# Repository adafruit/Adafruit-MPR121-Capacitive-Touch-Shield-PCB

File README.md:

## Adafruit MPR121 Capacitive Touch Shield PCB
<a href="http://www.adafruit.com/products/2024"><br/>
Click here to purchase one from the Adafruit shop</a>

This touch-able add on shield for Arduinos will inspire your next interactive project with 12 capacitive touch sensors. Capacitive touch sensing works by detecting when a person (or animal) has touched one of the sensor electrodes. Capacitive touch sensing used for stuff like touch-reactive tablets and phones, as well as control panels for appliances, which is where you may have used it before. This shield allows you to create electronics that can react to human touch, with up to 12 individual sensors.

The shield has 12 'figure 8' holes in it that can be gripped onto with alligator clip cables. Attach one side of the clip to the shield and the other side to something electrically conductive (like metal) or full of water (like vegetables or fruit!) Then start up our handy Arduino library to detect when the object is touched. That's pretty much it, very easy! For advanced users, you can also solder to a pad to make a slimmer & more permanent connection. Works great with any Arduino as it only uses the I2C pins (SCL & SDA).

It uses the same chip as our MPR121 12-Key Capacitive Touch Sensor Breakout so you can duplicate the library and code! We have examples for reading touches. Using an Arduino Leonardo and a little bit of creativity you can use it to turn touches into keyboard KeyUp/KeyDown presses (so you can make a veggie-keyboard) or pair it with our Music Maker shield to create an audio player that will play a sound per sensor (fruit drums!)

PCB files for the Adafruit MPR121 Capacitive Touch Shield. The format is EagleCAD schematic and board layout
- https://www.adafruit.com/product/2024

### License

Adafruit invests time and resources providing this open source design, please support Adafruit and open-source hardware by purchasing products from [Adafruit](https://www.adafruit.com)!

All text above must be included in any redistribution

Designed by Limor Fried/Ladyada for Adafruit Industries.
Creative Commons Attribution/Share-Alike, all text above must be included in any redistribution.
See license.txt for additional information.

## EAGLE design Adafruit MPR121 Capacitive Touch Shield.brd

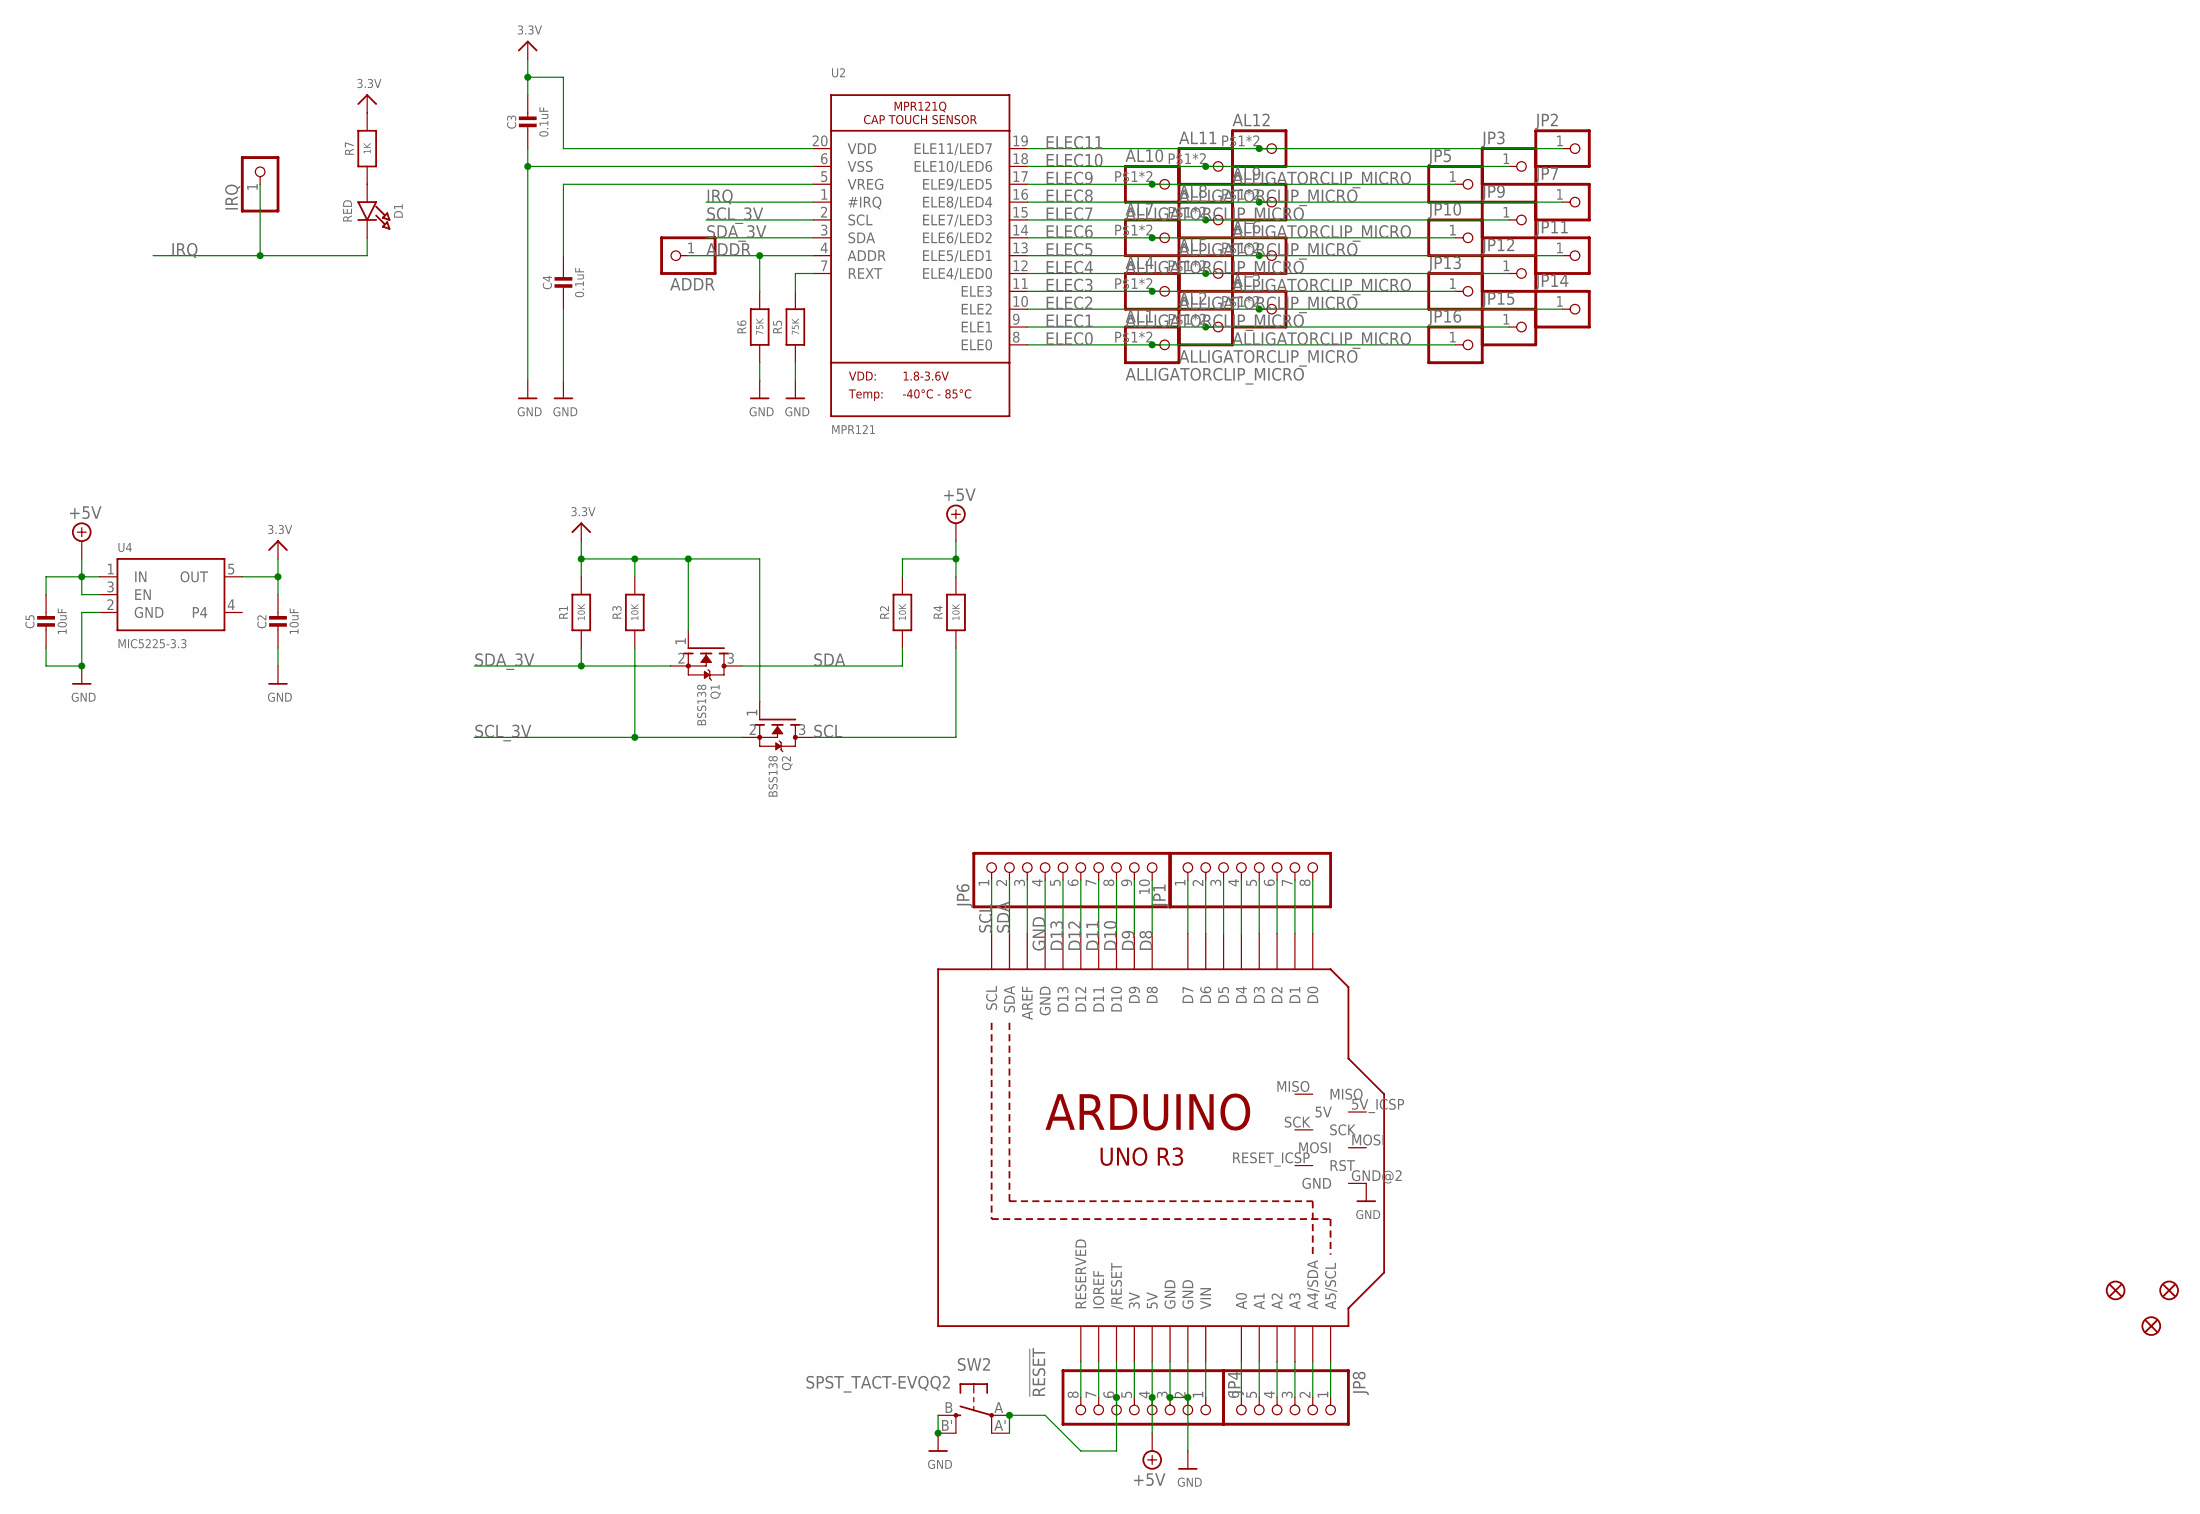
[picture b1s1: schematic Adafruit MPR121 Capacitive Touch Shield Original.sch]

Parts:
ADDR: HEADER-1X1ROUND; 1X01_ROUND
AL1, AL2, AL3, AL4, AL5, AL6, AL7, AL8, AL9, AL10, AL11, AL12: ALLIGATORCLIP_MICRO; ALLIGATORCLIP
C2, C5: 10uF; 0805-NO
C3, C4: 0.1uF; 0805-NO
D1: RED; CHIPLED_0805_NOOUTLINE
FID1, FID2, FID3: FIDUCIAL""; FIDUCIAL_1MM
IRQ: HEADER-1X1ROUND; 1X01_ROUND
JP1, JP4: PINHD-1X8CLEANBIG; 1X08-CLEANBIG
JP2, JP3, JP5, JP7, JP9, JP10, JP11, JP12, JP13, JP14, JP15, JP16: HEADER-1X1ROUND; 1X01_ROUND
JP6: HEADER-1X1070MIL; 1X10_ROUND70
JP8: PINHD-1X6CB; 1X06-CLEANBIG
Q1, Q2: BSS138; SOT23-WIDE
R1, R2, R3, R4: 10K; 0805-NO
R5, R6: 75K; 0805-NO
R7: 1K; 0805-NO
SW2: SPST_TACT-EVQQ2; EVQ-Q2
U2: MPR121; QFN20_3MM_NOTHERMAL
U4: MIC5225-3.3; SOT23-5
U$41: ARDUINO_R3_ICSP; ARDUINOR3_ICSP

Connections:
3.3V: C2.1, C3.1, Q1.1 (G), Q2.1 (G), R1.2, R3.2, R7.2, U2.20 (VDD), U4.5 (OUT); also elsewhere on the board
!RESET: JP4.6, SW2.A, SW2.A' (P1), U$41.RESET (/RESET)
+3V: JP4.5, U$41.3V
A0: JP8.6, U$41.A0
A1: JP8.5, U$41.A1
A2: JP8.4, U$41.A2
A3: JP8.3, U$41.A3
A4: JP8.2, U$41.A4 (A4/SDA)
A5: JP8.1, U$41.A5 (A5/SCL)
ADDR: ADDR.1, R6.2, U2.4 (ADDR)
AREF: JP6.3, U$41.AREF
D0: JP1.8, U$41.D0
D1: JP1.7, U$41.D1
D2: JP1.6, U$41.D2
D3: JP1.5, U$41.D3
D4: JP1.4, U$41.D4
D5: JP1.3, U$41.D5
D6: JP1.2, U$41.D6
D7: JP1.1, U$41.D7
D8: JP6.10, U$41.D8
D9: JP6.9, U$41.D9
D10: JP6.8, U$41.D10
D11: JP6.7, U$41.D11
D12: JP6.6, U$41.D12
D13: JP6.5, U$41.D13
ELEC0: AL1.P$1, AL1.P$2, JP16.1, U2.8 (ELE0)
ELEC1: AL2.P$1, AL2.P$2, JP15.1, U2.9 (ELE1)
ELEC2: AL3.P$1, AL3.P$2, JP14.1, U2.10 (ELE2)
ELEC3: AL4.P$1, AL4.P$2, JP13.1, U2.11 (ELE3)
ELEC4: AL5.P$1, AL5.P$2, JP12.1, U2.12 (ELE4/LED0)
ELEC5: AL6.P$1, AL6.P$2, JP11.1, U2.13 (ELE5/LED1)
ELEC6: AL7.P$1, AL7.P$2, JP10.1, U2.14 (ELE6/LED2)
ELEC7: AL8.P$1, AL8.P$2, JP9.1, U2.15 (ELE7/LED3)
ELEC8: AL9.P$1, AL9.P$2, JP7.1, U2.16 (ELE8/LED4)
ELEC9: AL10.P$1, AL10.P$2, JP5.1, U2.17 (ELE9/LED5)
ELEC10: AL11.P$1, AL11.P$2, JP3.1, U2.18 (ELE10/LED6)
ELEC11: AL12.P$1, AL12.P$2, JP2.1, U2.19 (ELE11/LED7)
GND: C2.2, C3.2, C4.2, C5.2, JP4.2, JP4.3, JP6.4, R5.1, R6.1, SW2.B (S), SW2.B' (S1), U2.6 (VSS), U4.2 (GND), U$41.GND, U$41.GND@1 (GND), U$41.GND@2 (GND), U$41.GND@3 (GND)
IRQ: D1.C, IRQ.1, U2.1 (#IRQ)
unnamed: C4.1, U2.5 (VREG)
unnamed: R5.2, U2.7 (REXT)
unnamed: D1.A, R7.1
NC: JP4.8, U$41.RESERVED
SCL: JP6.1, Q2.3 (D), R4.1, U$41.SCL
SCL_3V: Q2.2 (S), R3.1, U2.2 (SCL)
SDA: JP6.2, Q1.3 (D), R2.1, U$41.SDA
SDA_3V: Q1.2 (S), R1.1, U2.3 (SDA)
VIN: JP4.1, U$41.VIN

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
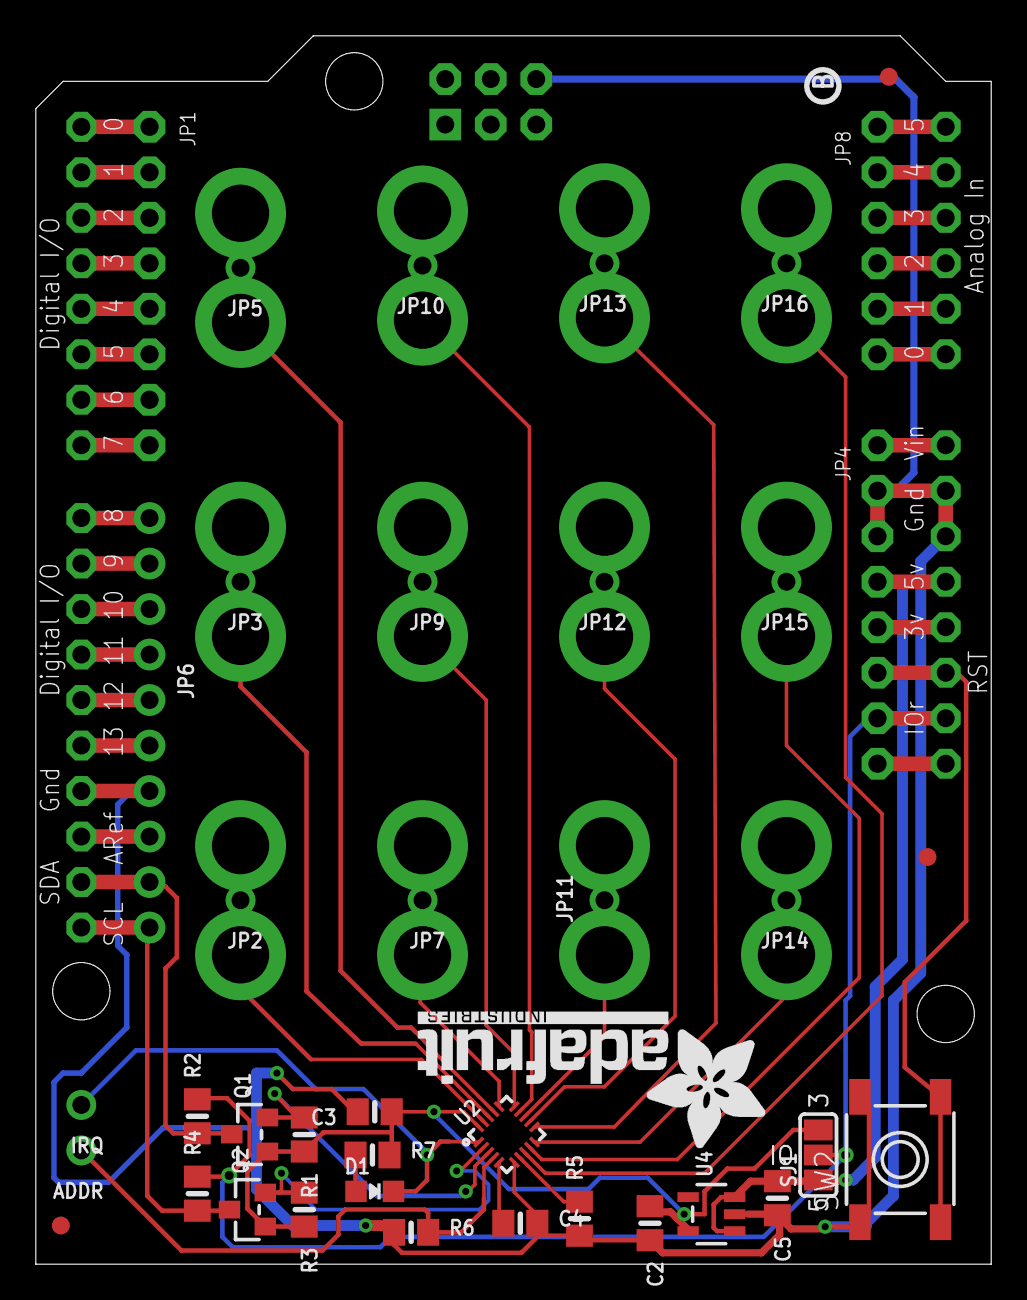
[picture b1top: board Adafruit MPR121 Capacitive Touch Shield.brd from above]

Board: 2 copper layers, 53.3 x 68.6 mm, 72 parts (0 on the bottom side), 50 nets.

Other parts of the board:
PLABEL0: PLABEL0
PLABEL1: PLABEL1
PLABEL2: PLABEL2
PLABEL3: PLABEL3
PLABEL4: PLABEL4
PLABEL5: PLABEL5
PLABEL6: PLABEL6
PLABEL7: PLABEL7
PLABEL8: PLABEL8
PLABEL9: PLABEL9
PLABEL10: PLABEL10
PLABEL11: PLABEL11
PLABEL12: PLABEL12
PLABEL13: PLABEL13
PLABEL14: PLABEL14
PLABEL15: PLABEL15
PLABEL16: PLABEL16
PLABEL17: PLABEL17
SJ1: SOLDERJUMPER_2WAY_OPEN_NOPASTE
U$8: PCBFEAT-REV-040
U$9: ADAFRUIT_TEXT_20MM

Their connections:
3.3V: SJ1.3; also elsewhere on the board

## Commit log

2016-08-08 init
2023-03-16 Add updated board files.
